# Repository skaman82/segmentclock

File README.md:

# segmentclock (WORK IN PROGRESS)
Arduino 7-Segment RGB LED Clock 

# Functions
- Colorfull 7-segments clock with multiple color presets</br>
- Auto LED brightness adjustment (optional)</br>
- Support sensor like Si7021(for temperature + humidity)</br>
- Alarm function</br>
- IR Remote (optional)</br>
- Web Weather forecast (not finished yet)</br>
- Optional Radio Module: PT2257, RDA5807M or SI4703 supported (requires IR function)</br>

…</br></br>

# Materials
- 5V WS2812b Led strip (60 LEDS/m) or 58x 2020 WS2812b LEDs and the custom segment PCB for the smaller version</br>
- 3x 6mm Pushbuttons</br>
- 3D-printed parts</br>
- DS3231 RTC Module (the small one)</br>
- ESP8266 D1 mini (or my custom PCB)</br>
- Photo-Resistor (optional)</br>
- Si7021 Temperature Sensor (optional)</br>
- GY-MAX4466 Microphone Module (optional)</br>
- Some resistors (10k, 470R, 1k)</br>

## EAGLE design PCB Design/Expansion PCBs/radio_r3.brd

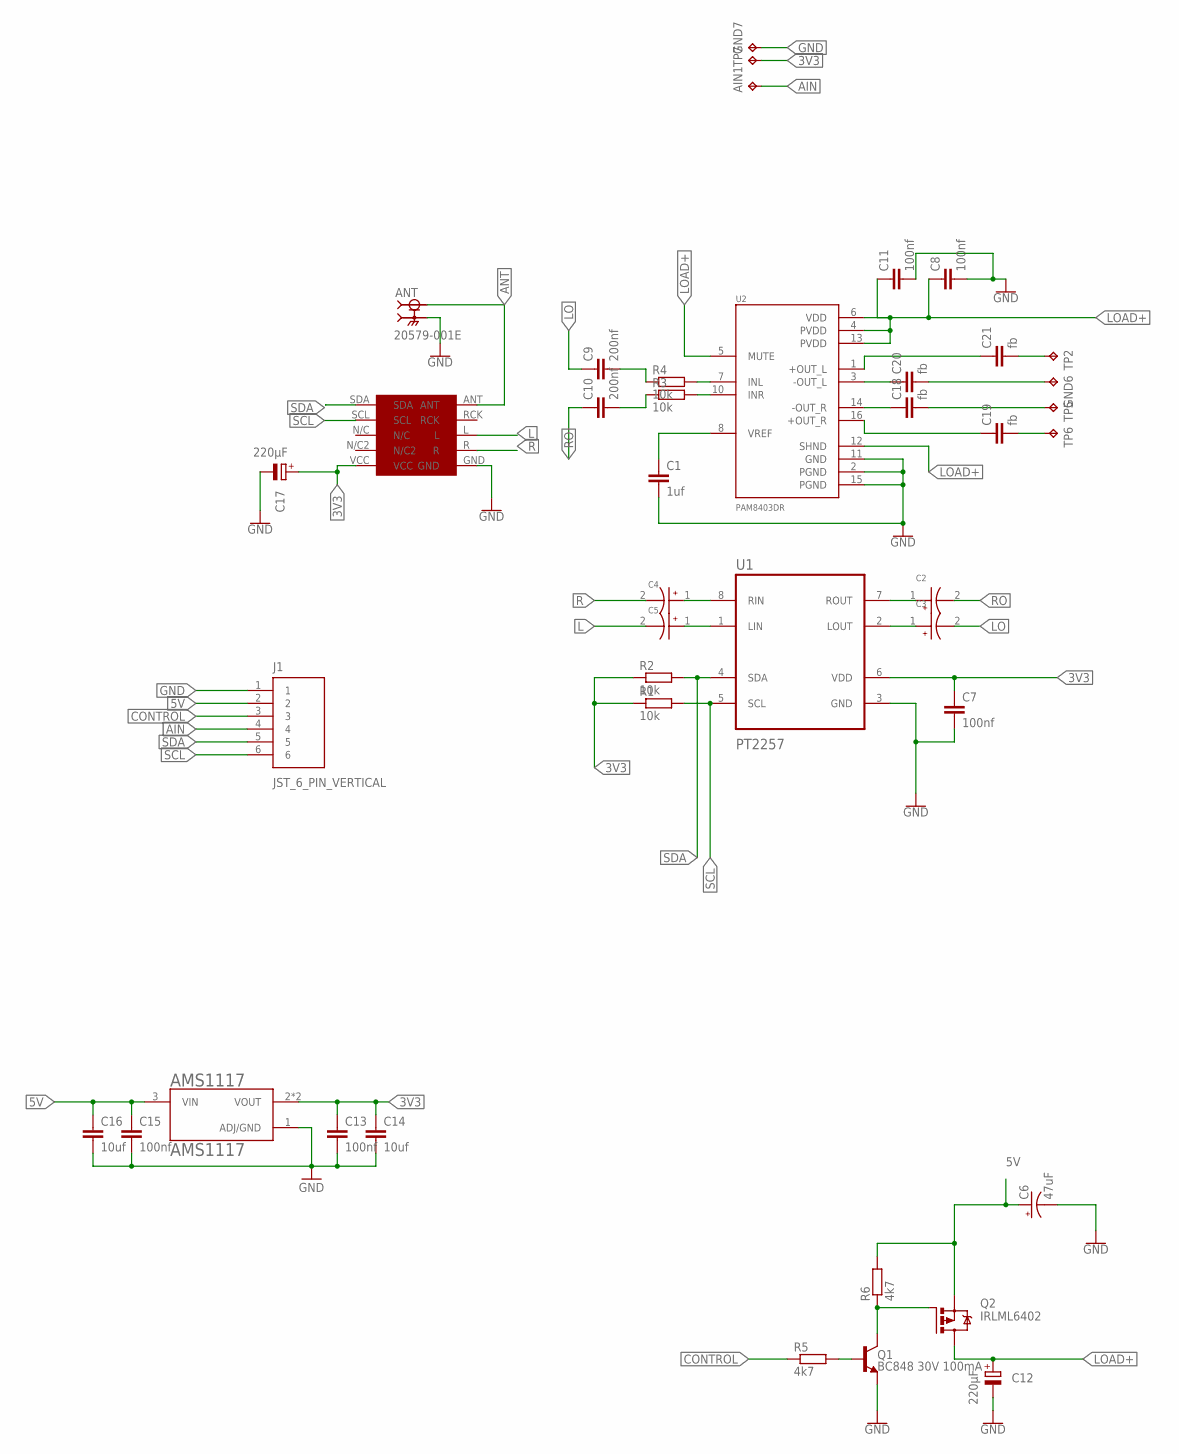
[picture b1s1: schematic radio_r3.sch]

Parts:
AIN1: TPTP10SQ; TP10SQ
AMS1117: AMS1117; SOT229P700X180-4N
ANT: 20579-001E; IPEX_20579-001E
C1: 1uf; C0805
C2, C3, C4, C5: 10uf; CAPMP3216X180N
C6: 47uF; EIA3528
C7, C13, C15: 100nf; C0603
C8, C11: 100nf; C0805
C9, C10: 200nf; C0805
C12, C17: 220µF; PANASONIC_D
C14, C16: 10uf; C0805
C18, C19, C20, C21: fb; C0805
GND6: TPTP15R; TP15R
GND7: TPTP10SQ; TP10SQ
J1: JST_6_PIN_VERTICAL; JST-6-SMD-VERT-1.0MM
Q1: BC848 30V 100mA; SOT23-3
Q2: IRLML6402; MICRO3
R1, R2: 10k; R0603
R3, R4: 10k; R0805
R5, R6: 4k7; R0603
RDA5807M: RDA
TP2, TP5, TP6: TPTP15R; TP15R
TP7: TPTP10SQ; TP10SQ
U1: PT2257; SOIC127P600X175-8N
U2: PAM8403DR; SOIC127P605X150-16N

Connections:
3V3: AMS1117.2 (VOUT), AMS1117.4 (VOUT), C7.1, C13.1, C14.1, C17.+, R1.1, R2.1, RDA5807M.VCC, TP7.TP, U1.6 (VDD)
5V: AMS1117.3 (VIN), C6.A (+), C15.1, C16.1, J1.2, Q2.2 (S), R6.2
AIN: AIN1.TP, J1.4
ANT: ANT.1 (SIGNAL), RDA5807M.ANT
CONTROL: J1.3, R5.1
GND: AMS1117.1 (ADJ/GND), ANT.G1 (GROUND), ANT.G2 (GROUND), ANT.G3 (GROUND), C1.2, C6.C (-), C7.2, C8.2, C11.2, C12.-, C13.2, C14.2, C15.2, C16.2, C17.-, GND7.TP, J1.1, Q1.2 (E), RDA5807M.GND, U1.3 (GND), U2.2 (PGND), U2.11 (GND), U2.15 (PGND)
L: C5.2, RDA5807M.L
LO: C3.2, C9.1
LOAD+: C8.1, C11.1, C12.+, Q2.3 (D), U2.4 (PVDD), U2.5 (MUTE), U2.6 (VDD), U2.12 (SHND), U2.13 (PVDD)
unnamed: Q1.1 (B), R5.2
unnamed: Q1.3 (C), Q2.1 (G), R6.1
unnamed: C2.1, U1.7 (ROUT)
unnamed: C3.1, U1.2 (LOUT)
unnamed: C1.1, U2.8 (VREF)
unnamed: C21.1, U2.1 (+OUT_L)
unnamed: C4.1, U1.8 (RIN)
unnamed: C5.1, U1.1 (LIN)
unnamed: C20.1, U2.3 (-OUT_L)
unnamed: C18.1, U2.14 (-OUT_R)
unnamed: C19.1, U2.16 (+OUT_R)
unnamed: R4.2, U2.7 (INL)
unnamed: R3.2, U2.10 (INR)
unnamed: C9.2, R4.1
unnamed: C10.2, R3.1
unnamed: C19.2, TP6.TP
unnamed: C18.2, TP5.TP
unnamed: C20.2, GND6.TP
unnamed: C21.2, TP2.TP
R: C4.2, RDA5807M.R
RO: C2.2, C10.1
SCL: J1.6, R1.2, RDA5807M.SCL, U1.5 (SCL)
SDA: J1.5, R2.2, RDA5807M.SDA, U1.4 (SDA)

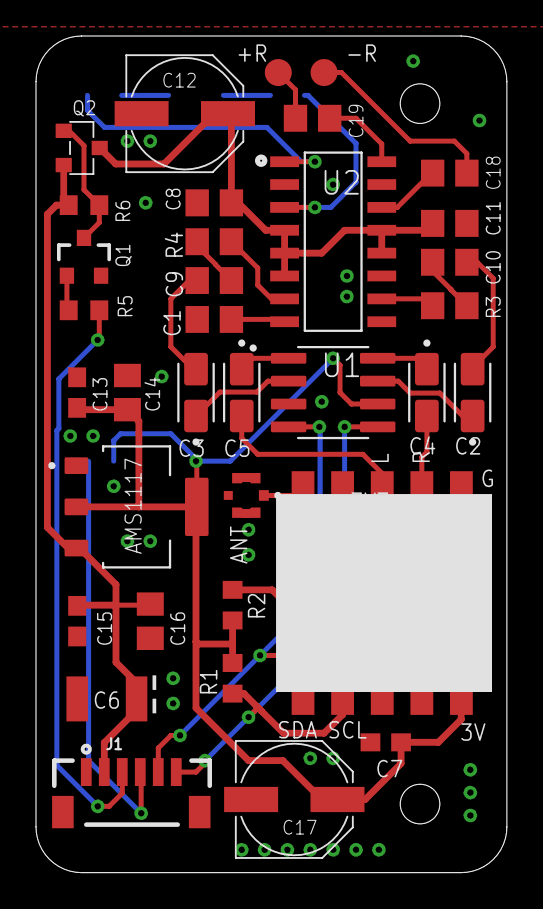
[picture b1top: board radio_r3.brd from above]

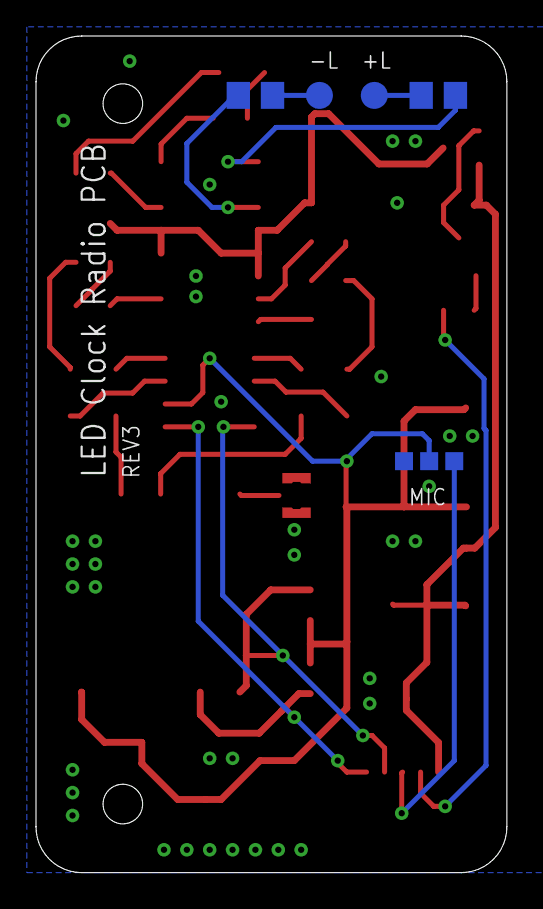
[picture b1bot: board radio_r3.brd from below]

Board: 2 copper layers, 26.1 x 46.4 mm, 42 parts (7 on the bottom side), 32 nets.

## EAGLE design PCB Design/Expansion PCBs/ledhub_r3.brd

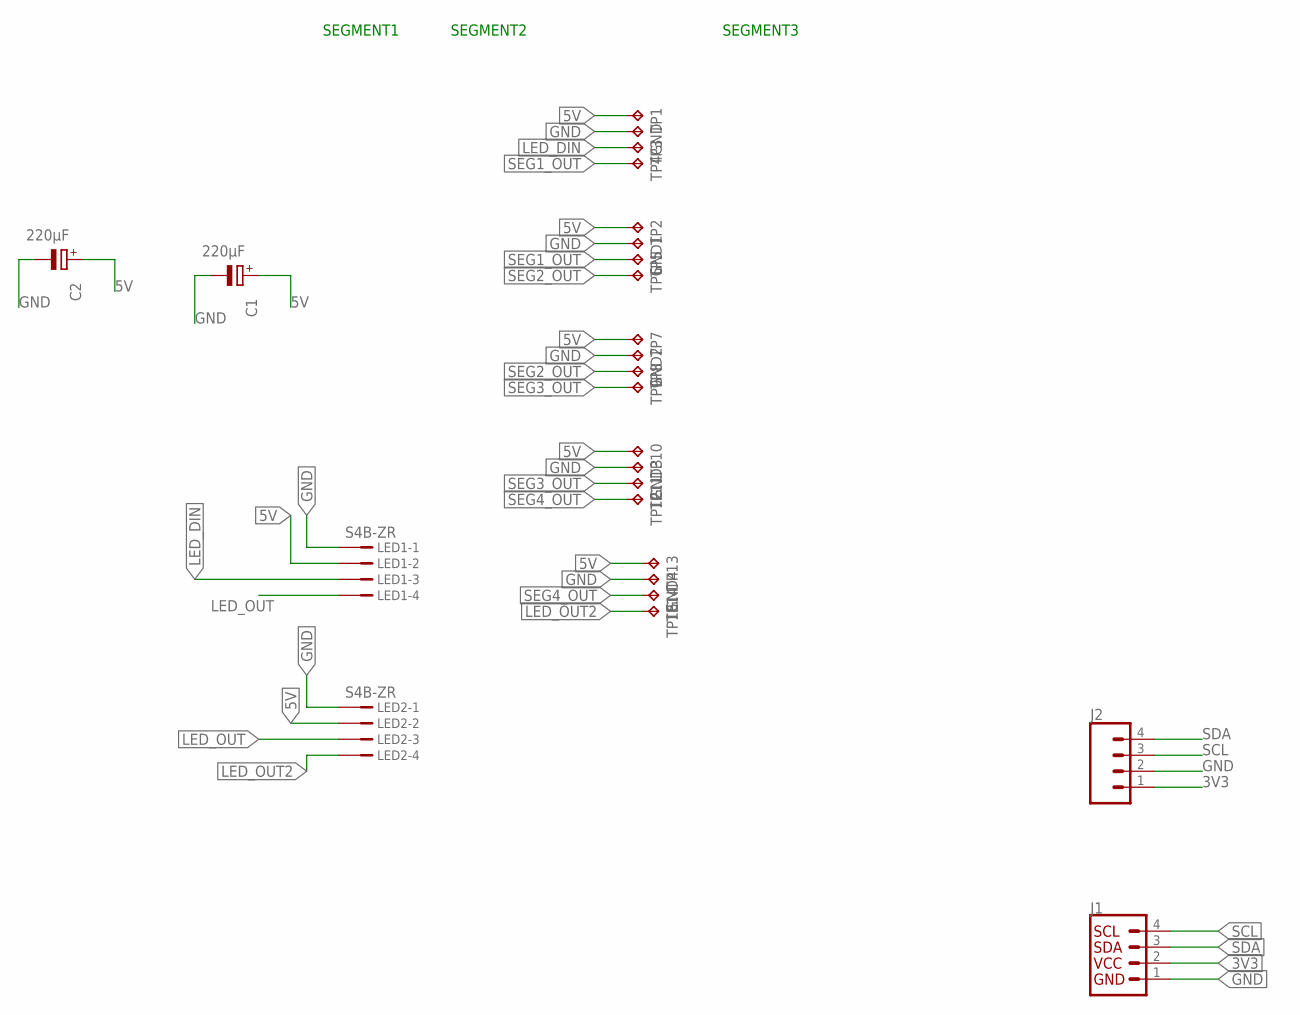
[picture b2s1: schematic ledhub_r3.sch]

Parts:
C1, C2: 220µF; PANASONIC_D
GND, GND1, GND2, GND3, GND4: TPTP15SQ; TP15SQ
J1: QWIIC_CONNECTORJS-1MM; 1X04_1MM_RA
J2: CONN_04; 1X04
LED1, LED2: S4B-ZR
TP1, TP2, TP3, TP4, TP5, TP6, TP7, TP8, TP9, TP10, TP11, TP12, TP13, TP14, TP15: TPTP15R; TP15R

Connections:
3V3: J1.2 (VCC), J2.1
5V: C1.+, C2.+, LED1.2, LED2.2, TP1.TP, TP2.TP, TP7.TP, TP10.TP, TP13.TP
GND: C1.-, C2.-, GND.TP, GND1.TP, GND2.TP, GND3.TP, GND4.TP, J1.1 (GND), J2.2, LED1.1, LED2.1
LED_DIN: LED1.3, TP3.TP
LED_OUT: LED1.4, LED2.3
LED_OUT2: LED2.4, TP15.TP
SCL: J1.4 (SCL), J2.3
SDA: J1.3 (SDA), J2.4
SEG1_OUT: TP4.TP, TP5.TP
SEG2_OUT: TP6.TP, TP8.TP
SEG3_OUT: TP9.TP, TP11.TP
SEG4_OUT: TP12.TP, TP14.TP

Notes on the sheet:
SEGMENT1
SEGMENT2
SEGMENT3

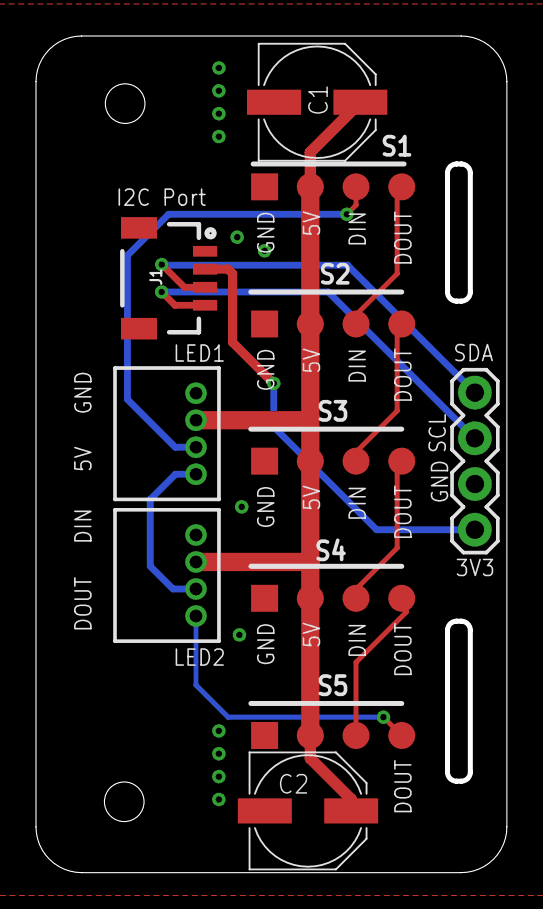
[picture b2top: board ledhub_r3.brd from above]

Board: 2 copper layers, 25.9 x 46.2 mm, 26 parts (0 on the bottom side), 12 nets.

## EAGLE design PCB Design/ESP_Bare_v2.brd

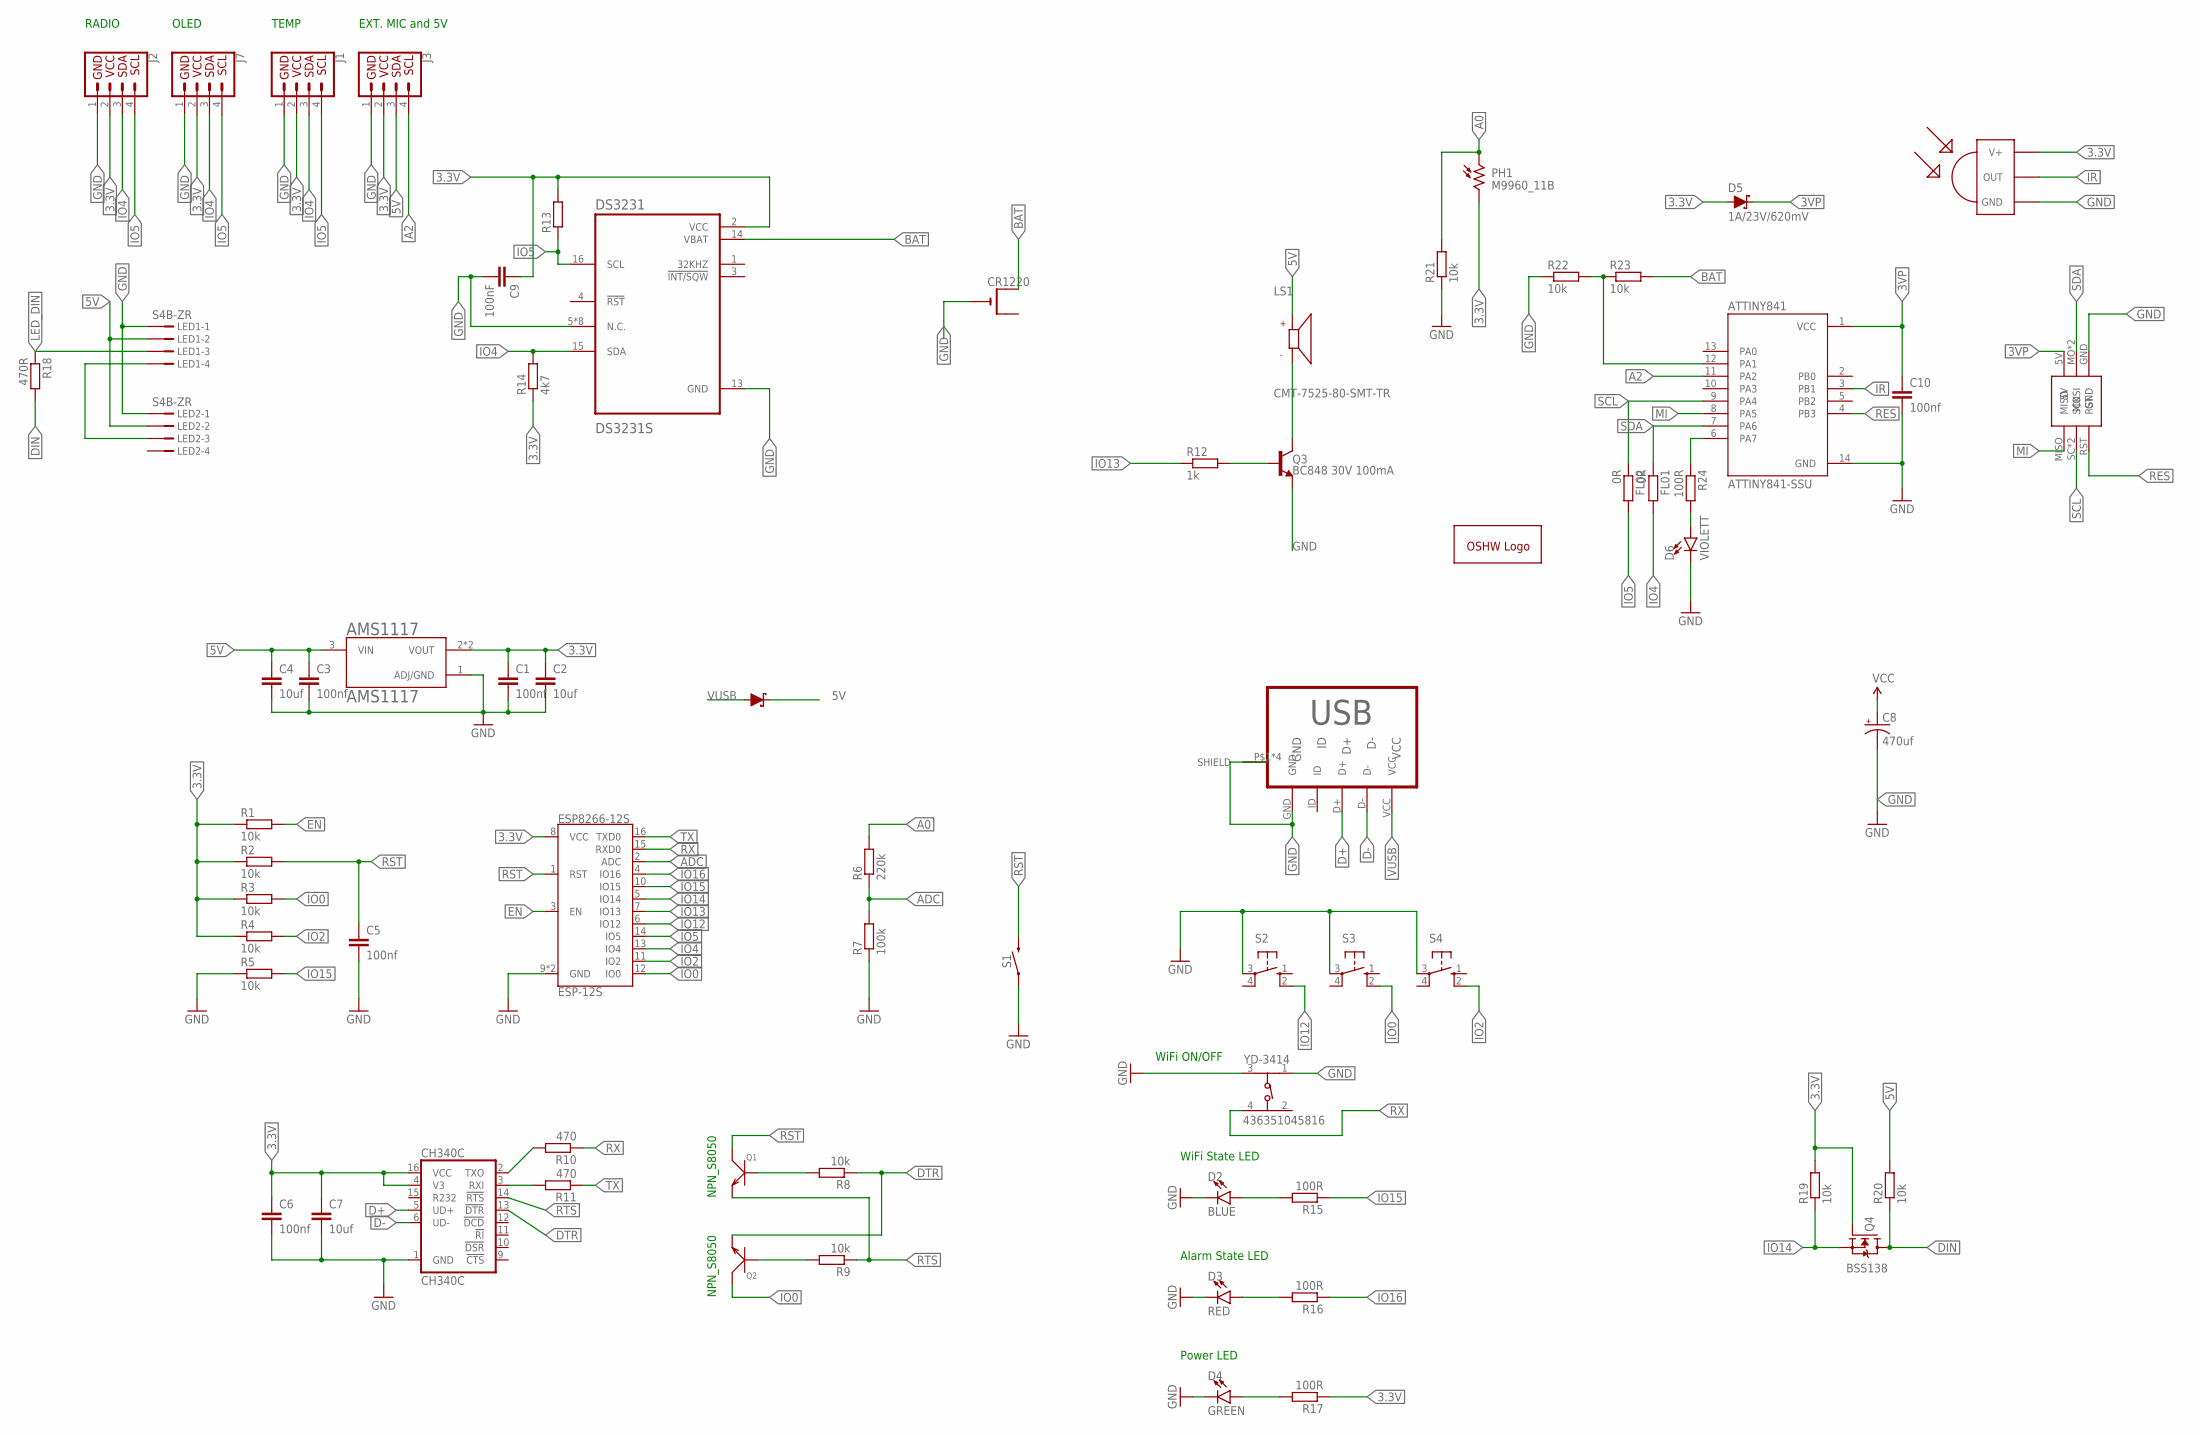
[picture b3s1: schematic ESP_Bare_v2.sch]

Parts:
AMS1117: AMS1117; SOT229P700X180-4N
ATTINY841: ATTINY841-SSU; SOIC127P599X175-14N
C1, C3, C5, C6, C10: 100nf; C0603
C2, C4: 10uf; C0805
C7: 10uf; C0603
C8: 470uf; EIA7343
C9: 100nF; C0603
CH340C: CH340C; SO016
CR1220: CR1220SMT; CR1220-SMD
D1: MBR130T1G, SL; SOD123 or SMA, 1A; SMA-DIODE
D2: BLUE; LED-0603
D3: RED; LED-0603
D4: GREEN; LED-0603
D5: 1A/23V/620mV; SOD-323
D6: VIOLETT; LED-0603
DS3231: DS3231S; SOIC127P1032X265-16N
ESP8266-12S: ESP-12S
FL01, FL02: 0R; R0603
GOLD_ORB_SM1: OSHWLOGOLOGO5MM; OSHW_5MM
J1, J2, J3, J7: QWIIC_CONNECTORJS-1MM; 1X04_1MM_RA
LED1, LED2: S4B-ZR
LS1: CMT-7525-80-SMT-TR; XDCR_CMT-7525-80-SMT-TR
MICRO-USB: MICRO-USB-B; MICRO_USB_4_LEGS
PH1: M9960_11B; M9960
Q1, Q2: NPN_S8050; SOT-23
Q3: BC848 30V 100mA; SOT23-3
Q4: BSS138; SOT95P240X111-3N
R1, R2, R3, R4, R5, R8, R9, R19, R20, R21, R22, R23: 10k; R0603
R6: 220k; R0603
R7: 100k; R0603
R10, R11: 470; R0603
R12: 1k; R0603
R13, R14: 4k7; R0603
R15, R16, R17, R24: 100R; R0603
R18: 470R; R0603
S1: MOMENTARY-SWITCH-SPST-SMD-4.6X2.8MM; TACTILE_SWITCH_SMD_4.6X2.8MM
S2, S3, S4: 10-XX; B3F-10XX
U$1: ISCP_PORTPOGONEW; ISCP_PADS_2ROW2HNEW
U$2: TSOP4838; TSOP18XX
YD-3414: 436351045816; 4363X10458XX

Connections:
3.3V: AMS1117.2 (VOUT), AMS1117.4 (VOUT), C1.1, C2.1, C6.1, C7.1, C9.1, CH340C.4 (V3), CH340C.16 (VCC), D5.A, DS3231.2 (VCC), ESP8266-12S.8 (VCC), J1.2 (VCC), J2.2 (VCC), J3.2 (VCC), J7.2 (VCC), PH1.2, Q4.1 (G), R1.1, R2.1, R3.1, R4.1, R13.2, R14.1, R17.1, R19.2, U$2.VCC (V+)
3VP: ATTINY841.1 (VCC), C10.1, D5.C, U$1.5V
5V: AMS1117.3 (VIN), C3.1, C4.1, C8.A (+), D1.C, J3.3 (SDA), LED1.2, LED2.2, LS1.P, R20.2
A0: PH1.1, R6.2, R21.2
A2: ATTINY841.11 (PA2), J3.4 (SCL)
ADC: ESP8266-12S.2 (ADC), R6.1, R7.2
BAT: CR1220.+$1 (+), DS3231.14 (VBAT), R23.2
D+: CH340C.5 (UD+), MICRO-USB.D+
D-: CH340C.6 (UD-), MICRO-USB.D-
DIN: Q4.3 (D), R18.2, R20.1
DTR: CH340C.13 (!DTR), Q2.2 (E), R8.1
EN: ESP8266-12S.3 (EN), R1.2
GND: AMS1117.1 (ADJ/GND), ATTINY841.14 (GND), C1.2, C2.2, C3.2, C4.2, C5.2, C6.2, C7.2, C8.C (-), C9.2, C10.2, CH340C.1 (GND), CR1220.-, D2.C, D3.C, D4.C, D6.C, DS3231.5 (N.C.), DS3231.6 (N.C.), DS3231.7 (N.C.), DS3231.8 (N.C.), DS3231.9 (N.C.), DS3231.10 (N.C.), DS3231.11 (N.C.), DS3231.12 (N.C.), DS3231.13 (GND), ESP8266-12S.9 (GND), ESP8266-12S.P$1 (GND), J1.1 (GND), J2.1 (GND), J3.1 (GND), J7.1 (GND), LED1.1, LED2.1, MICRO-USB.GND, MICRO-USB.P$1 (SHIELD), MICRO-USB.P$2 (SHIELD), MICRO-USB.P$3 (SHIELD), MICRO-USB.P$5 (SHIELD), Q3.2 (E), R5.1, R7.1, R21.1, R22.1, S1.1, S1.2 (1), S2.3, S3.3, S4.3, U$1.GND, U$2.GND, YD-3414.1 (3), YD-3414.3 (1)
IO0: ESP8266-12S.12 (IO0), Q2.3 (C), R3.2, S3.2 (S1)
IO2: ESP8266-12S.11 (IO2), R4.2, S4.2 (S1)
IO4: DS3231.15 (SDA), ESP8266-12S.13 (IO4), FL01.2, J1.3 (SDA), J2.3 (SDA), J7.3 (SDA), R14.2
IO5: DS3231.16 (SCL), ESP8266-12S.14 (IO5), FL02.2, J1.4 (SCL), J2.4 (SCL), J7.4 (SCL), R13.1
IO12: ESP8266-12S.6 (IO12), S2.2 (S1)
IO13: ESP8266-12S.7 (IO13), R12.1
IO14: ESP8266-12S.5 (IO14), Q4.2 (S), R19.1
IO15: ESP8266-12S.10 (IO15), R5.2, R15.1
IO16: ESP8266-12S.4 (IO16), R16.1
IR: ATTINY841.3 (PB1), U$2.OUT
LED_DIN: LED1.3, R18.1
MI: ATTINY841.8 (PA5), U$1.MISO
unnamed: Q3.1 (B), R12.2
unnamed: LED1.4, LED2.3
unnamed: Q1.1 (B), R8.2
unnamed: Q2.1 (B), R9.2
unnamed: ATTINY841.12 (PA1), R22.2, R23.1
unnamed: D6.A, R24.2
unnamed: ATTINY841.6 (PA7), R24.1
unnamed: D3.A, R16.2
unnamed: D2.A, R15.2
unnamed: D4.A, R17.2
unnamed: CH340C.3 (RXI), R11.2
unnamed: CH340C.2 (TXO), R10.2
unnamed: LS1.N, Q3.3 (C)
RES: ATTINY841.4 (PB3), U$1.RST
RST: C5.1, ESP8266-12S.1 (RST), Q1.3 (C), R2.2, S1.3 (2), S1.4 (2)
RTS: CH340C.14 (!RTS), Q1.2 (E), R9.1
RX: ESP8266-12S.15 (RXD0), R10.1, YD-3414.4 (2)
SCL: ATTINY841.9 (PA4), FL02.1, U$1.SC (SCK), U$1.SCK
SDA: ATTINY841.7 (PA6), FL01.1, U$1.MO (MOSI), U$1.MOSI
TX: ESP8266-12S.16 (TXD0), R11.1
VUSB: D1.A, MICRO-USB.VCC

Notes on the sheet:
NPN_S8050
WiFi ON/OFF
WiFi State LED
Alarm State LED
Power LED
OLED
TEMP
RADIO
EXT. MIC and 5V

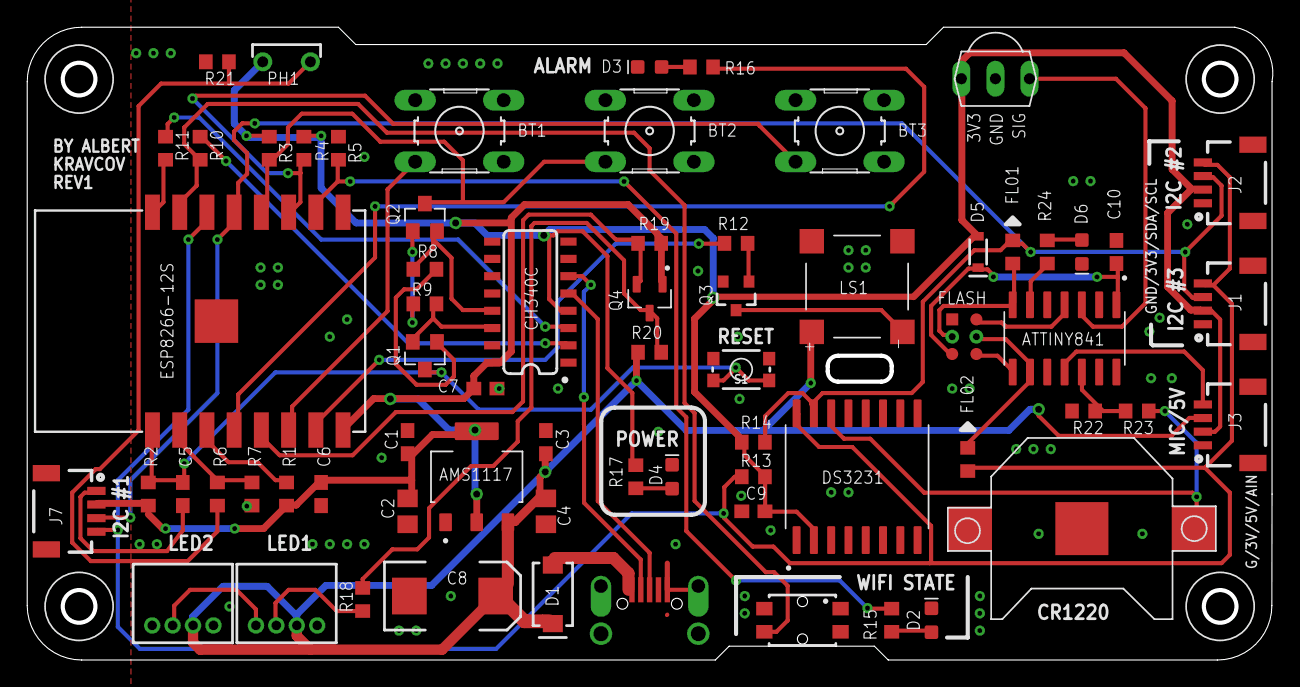
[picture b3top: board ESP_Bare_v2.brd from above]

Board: 2 copper layers, 91.2 x 46.2 mm, 69 parts (1 on the bottom side), 46 nets.

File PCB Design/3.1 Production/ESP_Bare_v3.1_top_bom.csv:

Comment,Designator,Footprint,LCSC Part #;
,CR1220,CR1220-SMD,;
,J1 J2 J3 J7,1X04_1MM_RA,;
 MBR130T1G  SL; SOD123 or SMA  1A,D1,SMA-DIODE,
0R,FL01 FL02,R0603,;
BAT20JFILM,D5,SOD-323,;
1k,R12,R0603,;
4k7,R13 R14,R0603,;
10k,R1 R2 R3 R4 R5 R8 R9 R19 R20 R21 R23,R0603,;
10uf,C2 C4,C0805,;
18k,R25,R0603,;
100R,R15 R16 R17 R24,R0603,;
100k,R7,R0603,;
100nF,C9,C0603,;
100nf,C1 C3 C5 C6 C7 C10,C0603,;
220k,R6,R0603,;
470,R10 R11 R18,R0603,;
470uf,C8,EIA7343,;
PTCF-V-T/R,YD-3414,4363X10458XX, C240298;
AMS1117,AMS1117,SOT229P700X180-4N,;
ATTINY841-SSU,ATTINY841,SOIC127P599X175-14N,;
BC848 30V 100mA,Q3,SOT23-3,;
BLUE,D2,LED-0603,;
BSS138,Q4,SOT95P240X111-3N,;
CH340C,CH340C,SO016,;
CMT-7525-80-SMT-TR,LS1,XDCR_CMT-7525-80-SMT-TR,;
DS3231S,DS3231,SOIC127P1032X265-16N,;
ESP-12F,ESP8266-12F,ESP-12F, C82891;
GREEN,D4,LED-0603,;
IRLML6344,Q5,SOT23,;
ISCP_PORTPOGONEW,U$1,ISCP_PADS_2ROW2HNEW,;
MICRO-USB-B,MICRO-USB,MICRO_USB_4_LEGS,;
MOMENTARY-SWITCH-SPST-SMD-4.6X2.8MM,S1 S5 S6 S7,TACTILE_SWITCH_SMD_4.6X2.8MM, C318893;
NPN_S8050,Q1 Q2,SOT-23,;
RED,D3,LED-0603,;
VIOLETT,D6,LED-0603,;

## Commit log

2021-01-08 upload code
2021-01-08 materials
2021-01-09 Average readout for temp und humidity sensors
2021-01-14 var additions
    • avg. measurements from DHT() and lightsensor()
    • WIFI Module Time-Sync (ESP8266 ESP-01)
    • Initial OLED support
2021-01-15 Refactoring
    • New RTC lib
    • Code refactoring as it was breaking the LED updates
2021-01-15 Imprvements
    • PopUp message handeling (OLED)
    • Sliding Pages (temp, humidity, time)
2021-01-15 small fix
2021-01-20 Updates
    • Alarm Support
    • EEPROM Support
2021-01-20 removing delays
2021-03-08 ESP8266 PCB and ATiny841 Code
2021-03-08 ESP Code state
2021-05-05 Fix issues
    • Fix WIFI button routing
    • Fix Photo-Resistor routing
2023-03-20 UPDATES
    • Final Clock PCP
    • ATtiny code: some changes
    • ESP code: more work done
2023-03-20 code cleanup
2023-03-21 popup cleanup
2023-03-21 fixes
    • Time setting (oled issue)
    • EN support for weekdays
    • Fahrenheit support
    • Changed min brightness
2023-03-21 cleanup
2023-03-22 added first icons
2023-03-22 icon pos change
2023-04-07 updates
    - new button handling
    - new Info menu (version, rtcbat, ip)
2023-04-07 fixed click management
2023-04-12 pcb update
2023-04-13 Btn management
    New button management including IR button handling

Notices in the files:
parts and their libraries:
SparkFun-Passives: Licensing: Creative Commons ShareAlike 4.0 International - https://creativecommons.org/licenses/by-sa/4.0
Eagle_WS-TASU: Copyright: Würth Elektronik
